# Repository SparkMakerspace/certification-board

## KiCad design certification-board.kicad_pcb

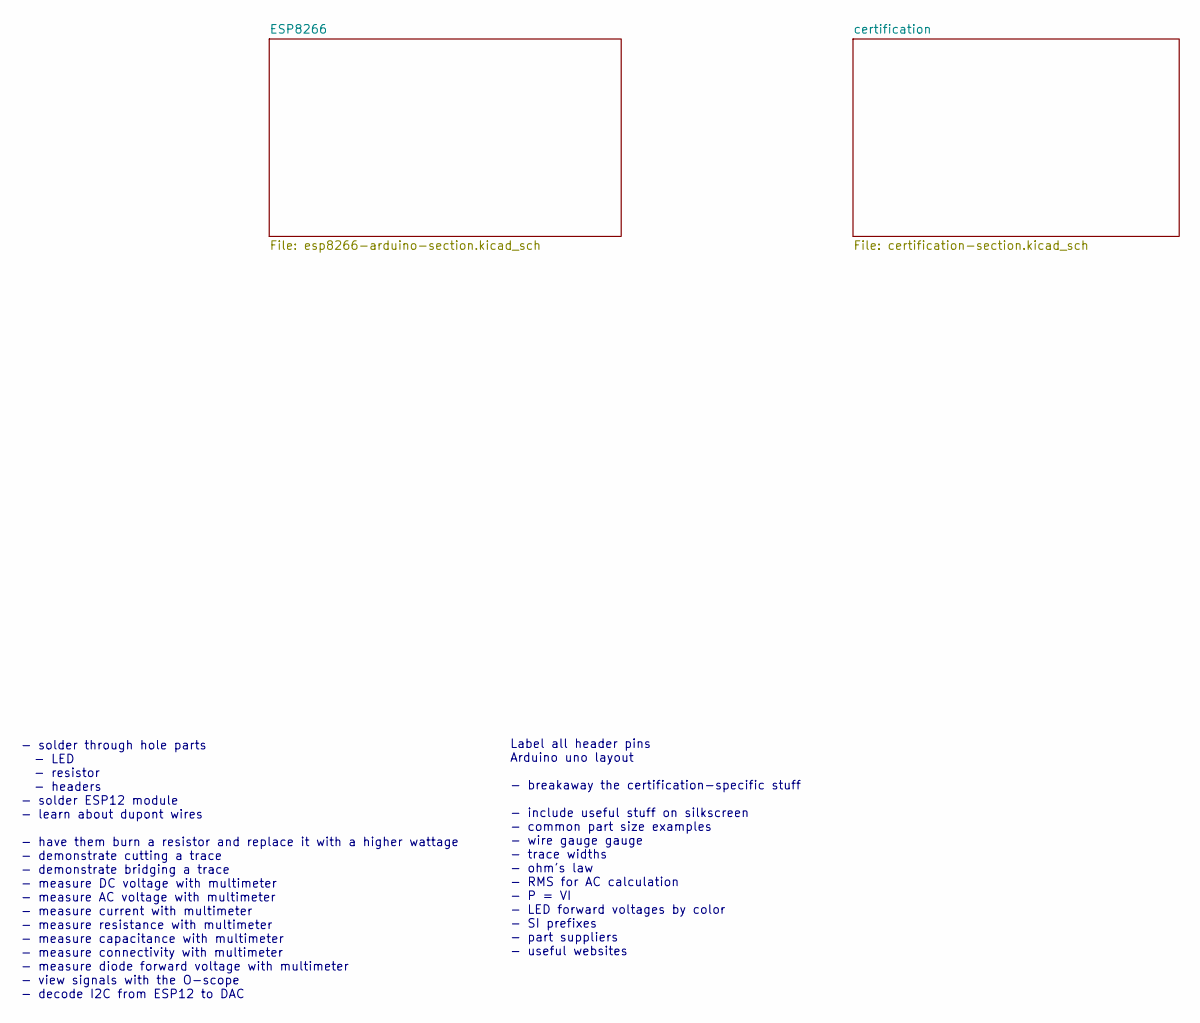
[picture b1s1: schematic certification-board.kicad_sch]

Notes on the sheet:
- solder through hole parts - LED - resistor - headers - solder ESP12 module - learn about dupont wires - have them burn a resistor and replace it with a higher wattage - demonstrate cutting a trace - demonstrate bridging a trace - measure DC voltage with multimeter - measure AC voltage with multim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
Label all header pins Arduino uno layout - breakaway the certification-specific stuff - include useful stuff on silkscreen - common part size examples - wire gauge gauge - trace widths - ohm's law - RMS for AC calculation - P = VI - LED forward voltages by color - SI prefixes - part suppliers - use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

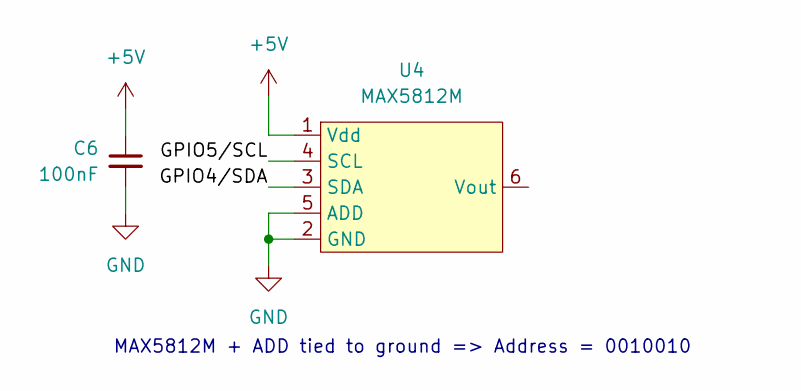
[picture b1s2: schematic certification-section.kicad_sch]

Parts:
C6: 100nF; C_0603_1608Metric; LCSC C14663
U4: MAX5812M; SOT-23-6

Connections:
+5V: C6.1, U4.1 (Vdd); also elsewhere on the board
/certification/GPIO4/SDA: U4.3 (SDA)
/certification/GPIO5/SCL: U4.4 (SCL)
GND: C6.2, U4.2 (GND), U4.5 (ADD); also elsewhere on the board

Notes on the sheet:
MAX5812M + ADD tied to ground => Address = 0010010

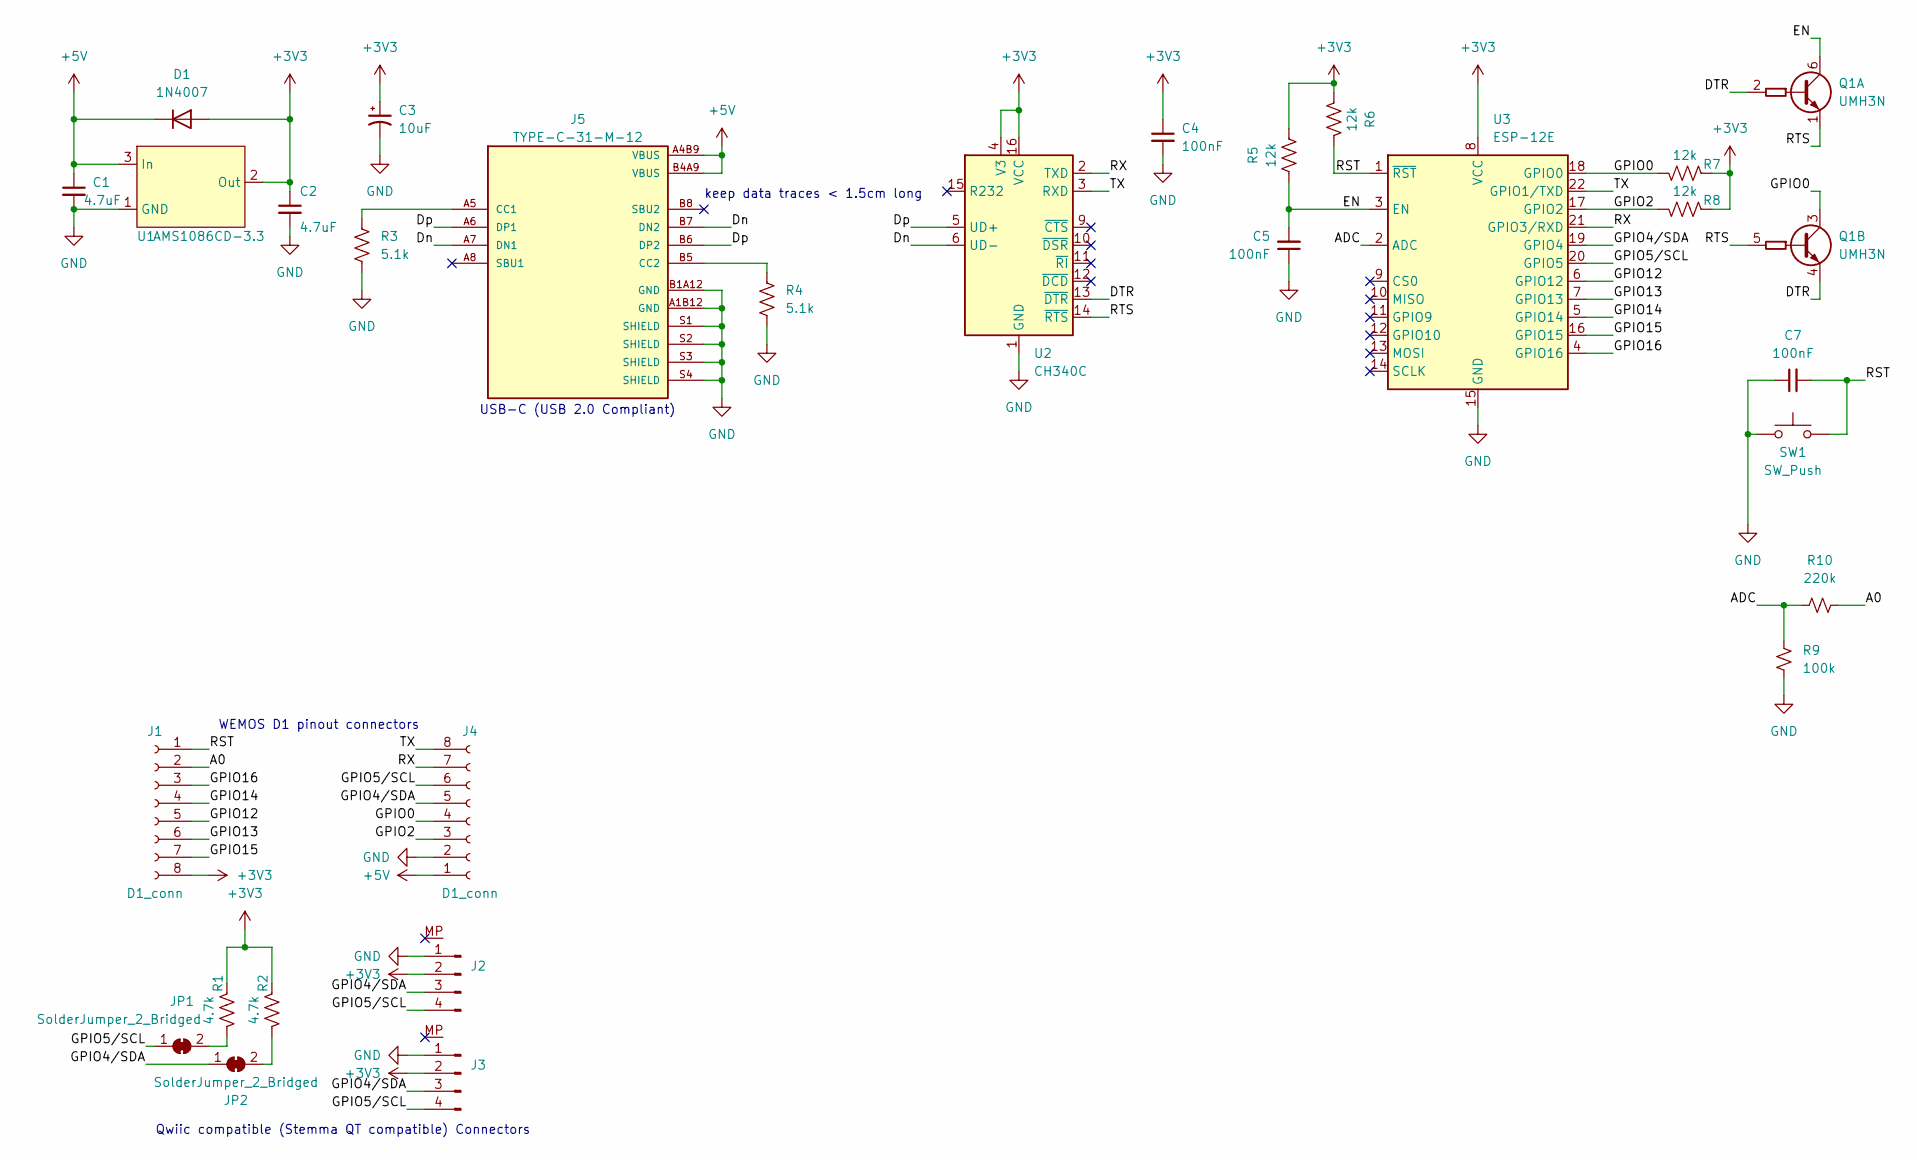
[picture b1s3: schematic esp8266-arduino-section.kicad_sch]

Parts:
C1, C2: 4.7uF; C_0603_1608Metric; LCSC C19666
C3: 10uF; CP_EIA-3216-18_Kemet-A; LCSC C7171
C4, C5, C7: 100nF; C_0603_1608Metric; LCSC C14663
D1: 1N4007; D_SMA; LCSC C727081
J1, J4: D1_conn; PinSocket_1x08_P2.54mm_Vertical
J2, J3: JST_SH_BM04B-SRSS-TB_1x04-1MP_P1.00mm_Vertical; LCSC C145956
J5: TYPE-C-31-M-12; HRO_TYPE-C-31-M-12; PARTREV A; LCSC C165948
JP1, JP2: SolderJumper_2_Bridged; SolderJumper-2_P1.3mm_Bridged_RoundedPad1.0x1.5mm
Q1: UMH3N; SOT-363_SC-70-6; LCSC C62892
R1, R2: 4.7k; R_0805_2012Metric; LCSC C17673
R3, R4: 5.1k; R_0805_2012Metric; LCSC C27834
R5, R6, R7, R8: 12k; R_0805_2012Metric; LCSC C17444
R9: 100k; R_0805_2012Metric; LCSC C149504
R10: 220k; R_0805_2012Metric; LCSC C17556
SW1: SW_Push; SW_SPST_SKQG_WithStem; LCSC C318884
U1: AMS1086CD-3.3; TO-252-2; LCSC C14241
U2: CH340C; SOIC-16_3.9x9.9mm_P1.27mm; LCSC C84681
U3: ESP-12E; LCSC C89297

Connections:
+3V3: C2.1, C3.1, C4.1, D1.2 (A), J1.8, J2.2, J3.2, R1.1, R2.1, R5.1, R6.1, R7.1, R8.1, U1.2 (Out), U2.4 (V3), U2.16 (VCC), U3.8 (VCC)
+5V: C1.1, D1.1 (K), J4.1, J5.A4B9 (VBUS), J5.B4A9 (VBUS), U1.3 (In); also elsewhere on the board
/ESP8266/A0: J1.2, R10.1
/ESP8266/ADC: R9.1, R10.2, U3.2 (ADC)
/ESP8266/DTR: Q1.2 (B1), Q1.4 (E2), U2.13 (~DTR)
/ESP8266/Dn: J5.A7 (DN1), J5.B7 (DN2), U2.6 (UD-)
/ESP8266/Dp: J5.A6 (DP1), J5.B6 (DP2), U2.5 (UD+)
/ESP8266/EN: C5.2, Q1.6 (C1), R5.2, U3.3 (EN)
/ESP8266/GPIO0: J4.4, Q1.3 (C2), R7.2, U3.18 (GPIO0)
/ESP8266/GPIO2: J4.3, R8.2, U3.17 (GPIO2)
/ESP8266/GPIO4/SDA: J2.3, J3.3, J4.5, JP2.1 (A), U3.19 (GPIO4)
/ESP8266/GPIO5/SCL: J2.4, J3.4, J4.6, JP1.1 (A), U3.20 (GPIO5)
/ESP8266/GPIO12: J1.5, U3.6 (GPIO12)
/ESP8266/GPIO13: J1.6, U3.7 (GPIO13)
/ESP8266/GPIO14: J1.4, U3.5 (GPIO14)
/ESP8266/GPIO15: J1.7, U3.16 (GPIO15)
/ESP8266/GPIO16: J1.3, U3.4 (GPIO16)
/ESP8266/RST: C7.2, J1.1, R6.2, SW1.2, U3.1 (~RST)
/ESP8266/RTS: Q1.1 (E1), Q1.5 (B2), U2.14 (~RTS)
/ESP8266/RX: J4.7, U2.2 (TXD), U3.21 (GPIO3/RXD)
/ESP8266/TX: J4.8, U2.3 (RXD), U3.22 (GPIO1/TXD)
GND: C1.2, C2.2, C3.2, C4.2, C5.1, C7.1, J2.1, J3.1, J4.2, J5.A1B12 (GND), J5.B1A12 (GND), J5.S1 (SHIELD), J5.S2 (SHIELD), J5.S3 (SHIELD), J5.S4 (SHIELD), R3.2, R4.2, R9.2, SW1.1, U1.1 (GND), U2.1 (GND), U3.15 (GND); also elsewhere on the board
unnamed: J5.A5 (CC1), R3.1
unnamed: J5.B5 (CC2), R4.1
unnamed: JP1.2 (B), R1.2
unnamed: JP2.2 (B), R2.2

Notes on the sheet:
USB-C (USB 2.0 Compliant)
keep data traces < 1.5cm long
Qwiic compatible (Stemma QT compatible) Connectors
WEMOS D1 pinout connectors

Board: 2 copper layers, 31 parts (2 on the bottom side), 26 nets, no tracks yet.
